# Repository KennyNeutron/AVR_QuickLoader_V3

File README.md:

# AVR QuickLoader V3

A unified hardware and software development repository for **AVR QuickLoader V3**—a high-performance AVR microcontroller programmer and desktop utility interface.

This project is divided into two primary directories:

*   **[`code/juan_flasher_desktop/`](./code/juan_flasher_desktop)**: The companion desktop application built with Electron, Vue 3, TypeScript, and Vite.
*   **[`pcb/`](./pcb)**: The KiCad hardware design files for the custom AVR QuickLoader V3 programmer board.

---

## Directory Structure

```text
AVR_QuickLoader_V3/
├── code/
│   └── juan_flasher_desktop/ # Desktop application software
│       ├── electron/          # Electron main process source
│       ├── src/               # Frontend source (Vue 3, TypeScript)
│       └── package.json       # Node package manager config
│
└── pcb/                   # Hardware design files
    └── AVR_QuickLoader_PCB_V1.0/
        ├── AVR_QuickLoader_PCB_V1.0.kicad_sch # KiCad Schematic
        └── AVR_QuickLoader_PCB_V1.0.kicad_pcb # KiCad PCB Layout
```

---

## 1. Hardware (`pcb/`)

The PCB folder contains the custom AVR programmer hardware designs.

*   **Design Tool**: KiCad
*   **Key Files**:
    *   Schematic: [AVR_QuickLoader_PCB_V1.0.kicad_sch](file:///D:/Projects/AVR_QuickLoader_V3/pcb/AVR_QuickLoader_PCB_V1.0/AVR_QuickLoader_PCB_V1.0.kicad_sch)
    *   Layout: [AVR_QuickLoader_PCB_V1.0.kicad_pcb](file:///D:/Projects/AVR_QuickLoader_V3/pcb/AVR_QuickLoader_PCB_V1.0/AVR_QuickLoader_PCB_V1.0.kicad_pcb)

---

## 2. Desktop Application (`code/juan_flasher_desktop/`)

A desktop application designed to control the AVR programmer and provide a rich dashboard for port diagnostics, HEX firmware uploads, and live serial monitoring.

### Key Features
*   **User Authentication**: Secure login system powered by Supabase with role-based access control (Admin/Temp roles).
*   **Cloud Firmware Management**: Browse, download, and flash firmware directly from cloud storage, or use local HEX files.
*   **Admin Dashboard**: Manage temporary user sessions and upload/delete firmware from the cloud.
*   **Modern UI/UX**: Sleek dark theme with frosted glass effects and JuanRobotix branding.

### Prerequisites

*   **Node.js** (v18 or v20 LTS recommended)
*   **npm** (Node Package Manager)

### Quick Start

To run the desktop application locally:

1.  Navigate into the `juan_flasher_desktop` directory:
    ```bash
    cd code/juan_flasher_desktop
    ```
2.  Install dependencies:
    ```bash
    npm install
    ```
3.  Launch the application in development mode:
    ```bash
    npm run dev
    ```

For detailed software configuration, npm scripts, and development guidelines, refer to the [code/juan_flasher_desktop/README.md](file:///D:/Projects/AVR_QuickLoader_V3/code/juan_flasher_desktop/README.md).

---

## License

This project is licensed under the MIT License.

## Updates
Last Updated: June 14, 2026

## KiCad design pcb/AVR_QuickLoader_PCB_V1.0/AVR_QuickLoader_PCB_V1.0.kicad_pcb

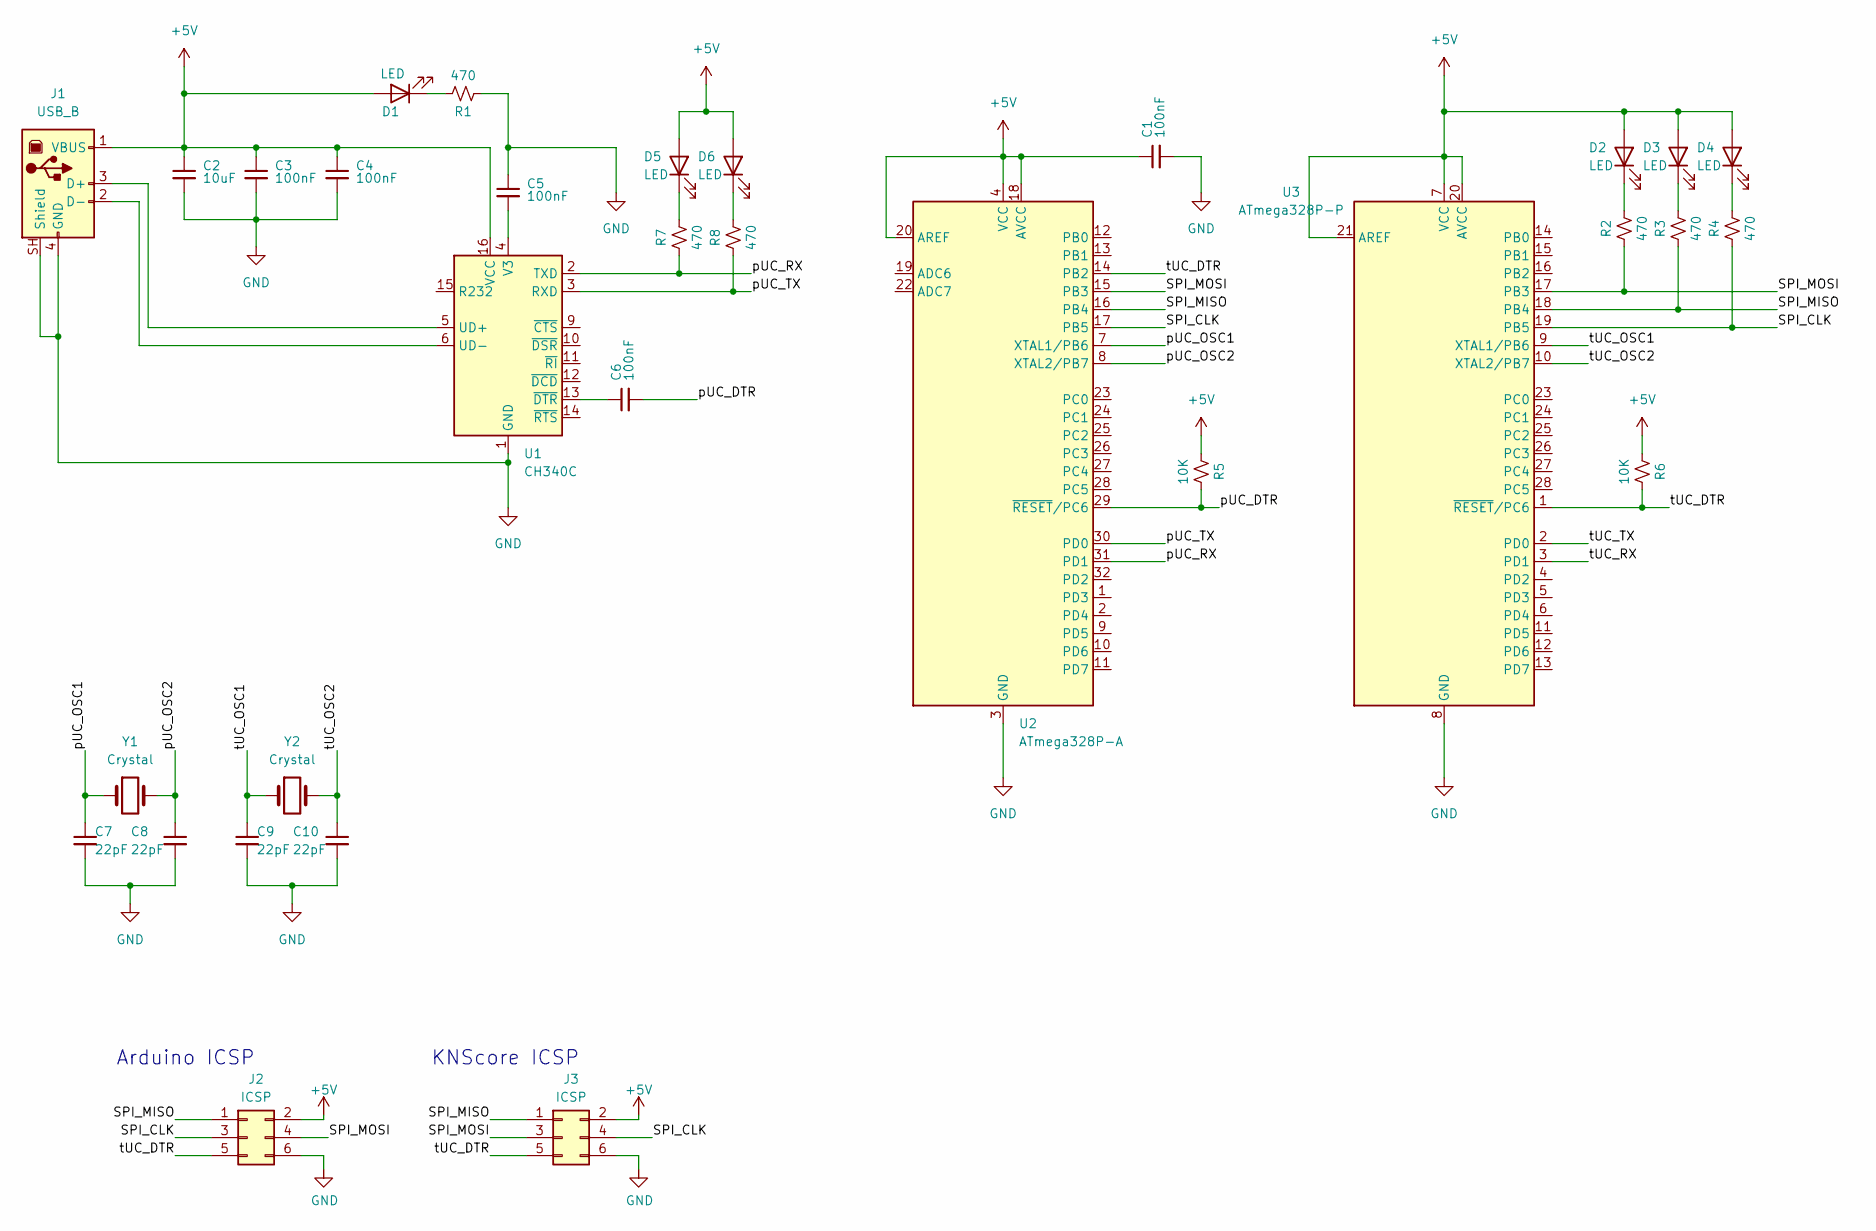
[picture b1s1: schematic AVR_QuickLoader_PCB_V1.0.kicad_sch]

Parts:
C1, C3, C4, C5, C6: 100nF; C_0805_2012Metric_Pad1.18x1.45mm_HandSolder
C2: 10uF; C_0805_2012Metric_Pad1.18x1.45mm_HandSolder
C7, C8, C9, C10: 22pF; C_0805_2012Metric_Pad1.18x1.45mm_HandSolder
D1, D2, D3, D4, D5, D6: LED; LED_D3.0mm
J1: USB_B; USB_B_Lumberg_2411_02_Horizontal
J2, J3: ICSP; PinHeader_2x03_P2.54mm_Vertical
R1, R2, R3, R4, R7, R8: 470; R_0805_2012Metric_Pad1.20x1.40mm_HandSolder
R5, R6: 10K; R_0805_2012Metric_Pad1.20x1.40mm_HandSolder
U1: CH340C; SOIC-16_3.9x9.9mm_P1.27mm
U2: ATmega328P-A; TQFP-32_7x7mm_P0.8mm
U3: ATmega328P-P; KennyNeutron_zif-28-pin
Y1, Y2: Crystal; Crystal_SMD_HC49-SD

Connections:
+5V: C1.1, C2.1, C3.1, C4.1, D1.2 (A), D2.2 (A), D3.2 (A), D4.2 (A), D5.2 (A), D6.2 (A), J1.1 (VBUS), J2.2, J3.2, R5.1, R6.1, U1.16 (VCC), U2.4 (VCC), U2.6 (VCC), U2.18 (AVCC), U2.20 (AREF), U3.7 (VCC), U3.20 (AVCC), U3.21 (AREF)
/SPI_CLK: J2.3, J3.4, R4.1, U2.17 (PB5), U3.19 (PB5)
/SPI_MISO: J2.1, J3.1, R3.1, U2.16 (PB4), U3.18 (PB4)
/SPI_MOSI: J2.4, J3.3, R2.1, U2.15 (PB3), U3.17 (PB3)
/pUC_DTR: C6.2, R5.2, U2.29 (~RESET/PC6)
/pUC_OSC1: C7.1, U2.7 (XTAL1/PB6), Y1.1
/pUC_OSC2: C8.1, U2.8 (XTAL2/PB7), Y1.2
/pUC_RX: R7.1, U1.2 (TXD), U2.31 (PD1)
/pUC_TX: R8.1, U1.3 (RXD), U2.30 (PD0)
/tUC_DTR: J2.5, J3.5, R6.2, U2.14 (PB2), U3.1 (~RESET/PC6)
/tUC_OSC1: C9.1, U3.9 (XTAL1/PB6), Y2.1
/tUC_OSC2: C10.1, U3.10 (XTAL2/PB7), Y2.2
/tUC_RX: U3.3 (PD1)
/tUC_TX: U3.2 (PD0)
GND: C1.2, C2.2, C3.2, C4.2, C5.1, C7.2, C8.2, C9.2, C10.2, J1.4 (GND), J1.SH (Shield), J2.6, J3.6, R1.1, U1.1 (GND), U2.3 (GND), U2.5 (GND), U2.21 (GND), U3.8 (GND), U3.22 (GND)
unnamed: D1.1 (K), R1.2
unnamed: D2.1 (K), R2.2
unnamed: D3.1 (K), R3.2
unnamed: D4.1 (K), R4.2
unnamed: D5.1 (K), R7.2
unnamed: D6.1 (K), R8.2
unnamed: J1.3 (D+), U1.5 (UD+)
unnamed: J1.2 (D-), U1.6 (UD-)
unnamed: C5.2, U1.4 (V3)
unnamed: C6.1, U1.13 (~DTR)

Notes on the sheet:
KNScore ICSP
Arduino ICSP

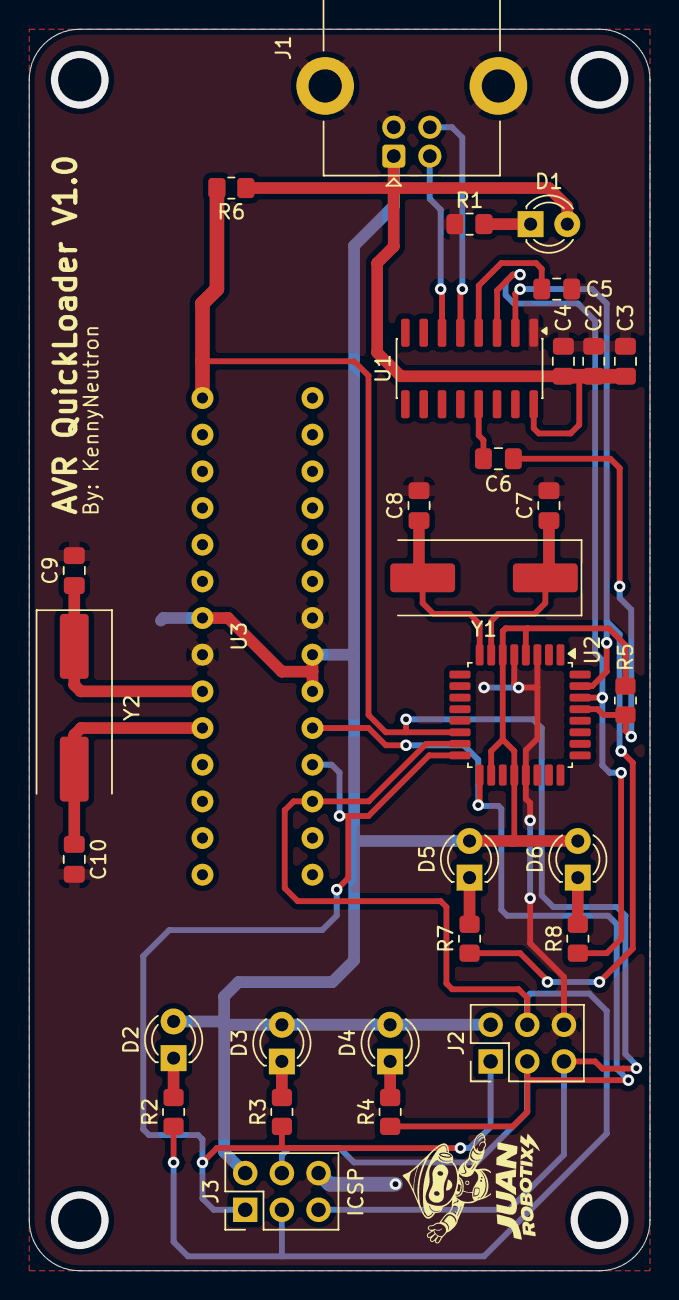
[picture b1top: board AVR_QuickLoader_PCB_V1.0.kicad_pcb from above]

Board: 2 copper layers, 43.0 x 86.0 mm, 32 parts (1 on the bottom side), 23 nets.

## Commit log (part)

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2026-01-27 feat: Initialize Electron, Vue 3, TypeScript, and Vite project with basic 'Hello World' app and comprehensive README.
2026-01-27 feat: Implement initial AVR QuickLoader UI layout and styling
2026-01-27 chore: Comment out Electron DevTools by default
2026-01-27 Auto stash before rebase of "main"
2026-01-27 Improves Electron app security and structure
    Migrates to contextIsolation for enhanced security by exposing ipcRenderer methods via contextBridge.
    Updates main process and preload script for better integration and removes unnecessary code.
    Switches to CommonJS modules for Electron build compatibility.
    Updates component to use the new exposed electron API.
2026-01-27 Enhances icon colors for visual clarity
    Improves the user interface by applying distinct colors to various icons within the application. This enhancement aids in quicker visual identification and improves the overall user experience.
2026-01-27 Implements firmware browse dialog and EOL options
    Adds functionality to browse for firmware files using a native dialog.
    Also introduces more comprehensive end-of-line (EOL) options for serial communication, including "No Line Ending", "Newline", "Carriage Return", and "Both NL & CR".
2026-01-27 Adds support for different programmers
    Extends bootloader burning and wiring test functionalities to support "Arduino as ISP" and "AVRISP mkII" programmers.
    This change introduces programmer-specific configurations, including setting the correct programmer type and passing extra arguments (like port and connection type) to `avrdude`.
2026-01-27 Improves terminal log handling and UI
    Refactors terminal log handling to support progress bars and improves serial message display.
    Adds a toggle to expand the terminal height for better visibility.
    The changes include:
    - Buffering of avrdude logs to correctly handle progress updates.
    - Improved serial data display by splitting lines and trimming whitespace.
    - Adds a toggle button to expand the terminal panel.
2026-01-27 Improves serial and terminal data handling
    Refactors serial data handling for better buffering and display, addressing issues with incomplete lines.
    Also enhances terminal log handling to correctly display progress updates.
    Updates styles to improve text wrapping in serial and terminal outputs.
2026-01-27 Improves serial terminal usability
    Adds autoscroll and clear log features to the serial terminal for a better user experience.
    The serial terminal now automatically scrolls to the bottom, keeping the latest messages in view. A button to clear the serial output is also added. The serial output is automatically cleared upon a 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
2026-01-28 feat: Implement the main application component with UI, logic, and styling for AVR QuickLoader.
2026-01-28 feat: Implement initial Electron application for AVR programming and serial monitoring with a Vue.js frontend.
2026-01-28 feat: Implement initial Electron application with Vue.js GUI for AVR firmware uploading and serial port management.
2026-01-28 feat: Implement the Electron main process, enabling AVR programming and serial communication.
2026-01-28 feat: Add initial core application UI for AVR QuickLoader with port selection, firmware upload, device configuration, and status display.
2026-01-28 feat: Add Electron Builder configuration and scripts for application distribution.
2026-04-20 updated main.ts and package.json
2026-06-01 rearranged files and folders
2026-06-01 deleted duplicate files in root dir
2026-06-03 added pcb files
2026-06-05 added readme and started the pcb design routing
2026-06-06 added readme updates
2026-06-07 update from ubuntu side - first commit
2026-06-08 finished pcb design
2026-06-09 refactored the arrangement on the SCH file
2026-06-10 Updates AVR QuickLoader PCB project
    Includes new project backup archives and reflects an update to the project's internal history. Also adjusts KiCad project preferences, setting a new active layer and clearing the layer preset.
2026-06-13 migrated in preparation for JUAN Flasher
2026-06-13 Adds user authentication and UI refresh
    Introduces a robust user authentication system powered by Supabase, including login, logout, and session restoration capabilities. This provides a dedicated login view to control access to the applic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
    Performs a significant UI/UX overhaul across the entire application. This includes integrating new JuanRobotix branding assets (logo and icon) and applying a modern dark theme with frosted glass effe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
    Bumps application version to 3.2.1.
2026-06-13 Adds admin panel for managing temporary user access
    Implements role-based access control with 'admin' and 'temp' user roles. Introduces a new Supabase RPC to allow authenticated administrators to create expiring temporary user accounts directly from t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
    Includes a new "Admin Control" dashboard tab that provides a UI for:
    - Generating temporary user credentials with specified durations.
    - Listing active and expired temporary user sessions.
    Enhances user session management by:
    - Fetching and displaying the user's role in the UI.
2026-06-13 Adds admin actions for temporary user management
    Introduces RPC functions `disable_temp_user` and `delete_temp_user` to the database, enabling administrators to expire or permanently remove temporary user accounts.
    Integrates these new actions into the temporary user table in the UI, providing 'Disable' and 'Delete' buttons for direct management. The 'Disable' action immediately expires a user's session, while 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
2026-06-13 Adds cloud firmware management and selection
    Introduces the ability to select firmware from either local files or a Supabase cloud storage bucket.
    Allows authenticated users to browse and download firmware from the cloud. Downloaded firmware is securely saved to a temporary local file by the Electron main process for use with `avrdude`.
    Provides administrators with additional functionality to upload and delete firmware directly to/from the cloud bucket.
    Updates the `database_setup.sql` script with detailed instructions and Supabase Storage policy definitions required for the new `firmware` bucket.
    Enhances the UI with a firmware source toggle, cloud firmware list, status indicators, and
2026-06-13 Clears firmware cache on logout and startup
    Adds an Electron IPC handler to recursively remove the temporary directory used for storing downloaded cloud firmware files.
    Invokes this cache clearing mechanism in two key situations:
    - On user logout: Ensures any user-specific downloaded firmware is removed, improving privacy and preventing accidental use of old data.
    - On application startup: Cleans up any potentially stale or leftover firmware files from previous sessions, providing a fresh state for the application.
2026-06-14 Adds key features section to README
    Enhances the README to provide a clear overview of the desktop application's main functionalities. Details key features such as user authentication, cloud firmware management, admin dashboard capabil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
    Also updates the last modified date.
2026-06-15 Improves application icon handling and Windows integration
    Introduces a `postinstall` script to patch the development Electron executable on Windows with the correct application icon. This ensures the custom icon is displayed in the taskbar during developmen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
    Sets the `AppUserModelId` for Windows, which enhances taskbar grouping and identification of the application.
    Updates the main window's icon loading to use `nativeImage` for better cross-platform compatibility and consistency, and corrects the icon path used during the final application build.
2026-06-22 Update AVR QuickLoader PCB project
    Incorporates adjustments to KiCad local settings, such as disabling auto track width and enhancing layer visibility, alongside new design backups and an updated subproject reference.
